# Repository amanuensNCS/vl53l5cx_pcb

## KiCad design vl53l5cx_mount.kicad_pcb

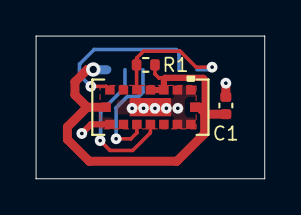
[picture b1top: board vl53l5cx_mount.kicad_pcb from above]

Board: 2 copper layers, 12.7 x 7.9 mm, 4 parts (1 on the bottom side), 6 nets.

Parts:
C1: 1u; C_0402_1005Metric
J1: Conn_01x06_MountingPin; JST_SH_BM06B-SRSS-TB_1x06-1MP_P1.00mm_Vertical
R1: 47k; R_0402_1005Metric
U1: VL53L5CXV0GC/1; VL53L5CX

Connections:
/INT: J1.6, R1.1, U1.A3 (GPIO1)
/RST: J1.5, U1.A1 (SPI_I2C_N)
/SCL: J1.2, U1.C4 (SCL/MCLK)
/SDA: J1.3, U1.C3 (SDA/MOSI)
Earth: C1.2, J1.4, J1.MP (MountPin), U1.A6 (GND), U1.A7 (GND), U1.B4 (THERMAL_PAD), U1.C1 (GNB), U1.C6 (GND), U1.C7 (GND)
VCC: C1.1, J1.1, R1.2, U1.A4 (IOVDD), U1.A5 (LP), U1.B1 (AVDD), U1.B7 (AVDD)

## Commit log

2022-03-28 reduced component count
2022-03-28 clean up DRC
2022-03-28 fix connector and edges
2022-03-28 update silkscreen
